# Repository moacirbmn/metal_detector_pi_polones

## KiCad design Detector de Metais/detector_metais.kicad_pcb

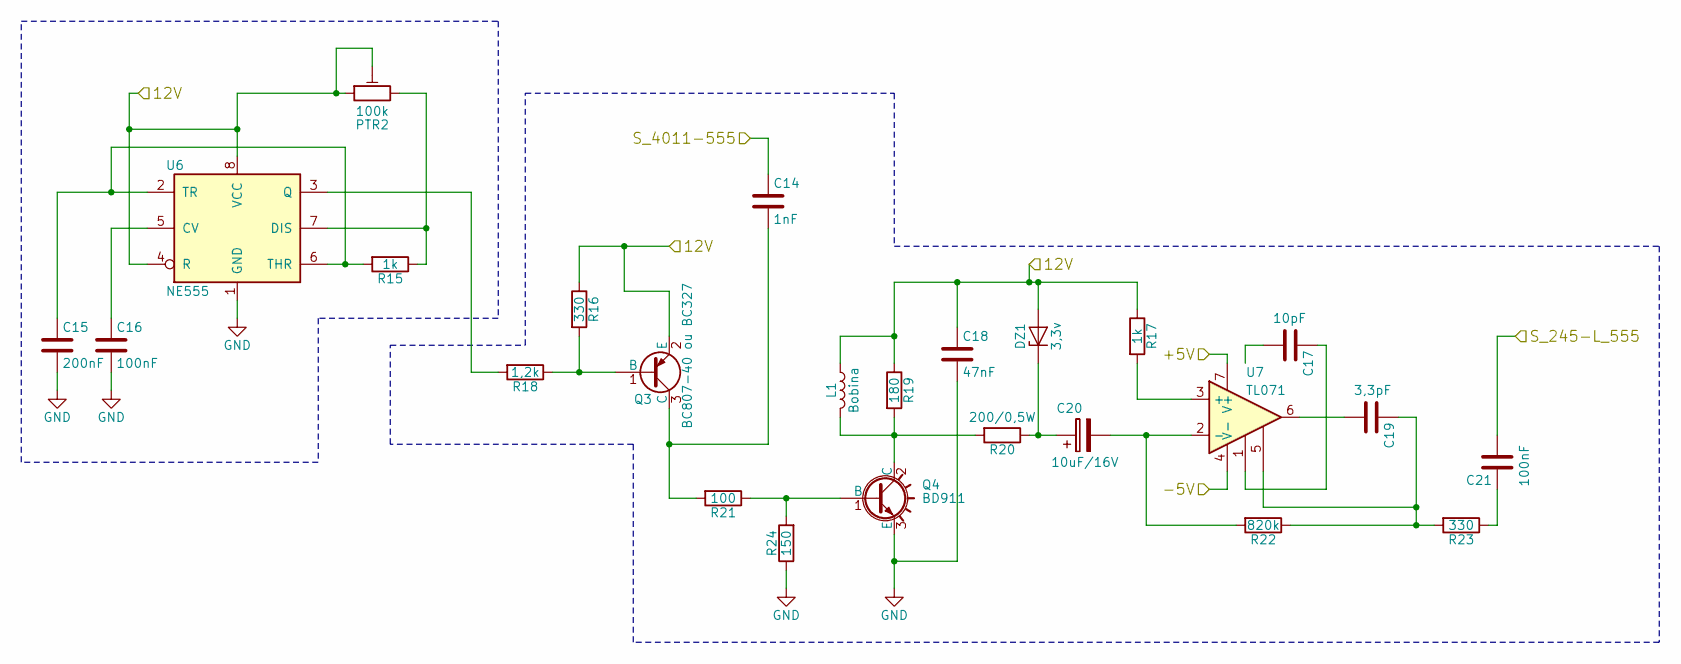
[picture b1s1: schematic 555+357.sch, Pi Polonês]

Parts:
C14: 1nF; C_Disc_D9.0mm_W5.0mm_P5.00mm
C15: 200nF; C_Disc_D6.0mm_W2.5mm_P5.00mm
C16, C21: 100nF; C_Disc_D4.3mm_W1.9mm_P5.00mm
C17: 10pF; C_Disc_D6.0mm_W2.5mm_P5.00mm
C18: 47nF; C_Disc_D6.0mm_W2.5mm_P5.00mm
C19: 3,3pF; C_Disc_D6.0mm_W2.5mm_P5.00mm
C20: 10uF/16V; C_Disc_D6.0mm_W2.5mm_P5.00mm
DZ1: 3,3v; D_A-405_P2.54mm_Vertical_AnodeUp
L1: Bobina; BarrelJack_Horizontal
PTR2: 100k; Potentiometer_ACP_CA9-H3,8_Horizontal
Q3: BC807-40 ou BC327; TO-92L
Q4: BD911; TO-220-3_Vertical
R15, R17: 1k; R_0805_2012Metric_Pad1.15x1.40mm_HandSolder
R16, R23: 330; R_0805_2012Metric_Pad1.15x1.40mm_HandSolder
R18: 1,2k; R_Axial_DIN0204_L3.6mm_D1.6mm_P1.90mm_Vertical
R19: 180; R_0805_2012Metric_Pad1.15x1.40mm_HandSolder
R20: 200/0,5W; R_Axial_DIN0207_L6.3mm_D2.5mm_P5.08mm_Vertical
R21: 100; R_0805_2012Metric_Pad1.15x1.40mm_HandSolder
R22: 820k; R_0805_2012Metric_Pad1.15x1.40mm_HandSolder
R24: 150; R_Axial_DIN0204_L3.6mm_D1.6mm_P1.90mm_Vertical
U6: NE555; HTSOP-8-1EP_3.9x4.9mm_P1.27mm_EP2.4x3.2mm
U7: TL071; DIP-8_W7.62mm_LongPads

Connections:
/555+357/12V: C18.1, DZ1.2 (A), L1.1, PTR2.1, PTR2.2, Q3.2 (E), R16.1, R17.1, R19.1, U6.4 (R), U6.8 (VCC); also elsewhere on the board
/555+357/+5V: U7.7 (V+); also elsewhere on the board
/555+357/-5V: U7.4 (V-); also elsewhere on the board
/555+357/S_245-L_555: C21.2; also elsewhere on the board
/4011/S_4011-555: C14.1; also elsewhere on the board
GND: C15.2, C16.2, C18.2, Q4.3 (E), R24.1, U6.1 (GND); also elsewhere on the board
unnamed: C14.2, Q3.3 (C), R21.2
unnamed: C15.1, R15.2, U6.2 (TR), U6.6 (THR)
unnamed: C16.1, U6.5 (CV)
unnamed: C17.1, U7.1
unnamed: C17.2, U7.8 (NC)
unnamed: C19.1, R22.1, R23.2, U7.5
unnamed: C19.2, U7.6
unnamed: C20.1, DZ1.1 (K), R20.1
unnamed: C20.2, R22.2, U7.2 (-)
unnamed: C21.1, R23.1
unnamed: L1.2, Q4.2 (C), R19.2, R20.2
unnamed: PTR2.3, R15.1, U6.7 (DIS)
unnamed: Q3.1 (B), R16.2, R18.1
unnamed: Q4.1 (B), R21.1, R24.2
unnamed: R17.2, U7.3 (+)
unnamed: R18.2, U6.3 (Q)

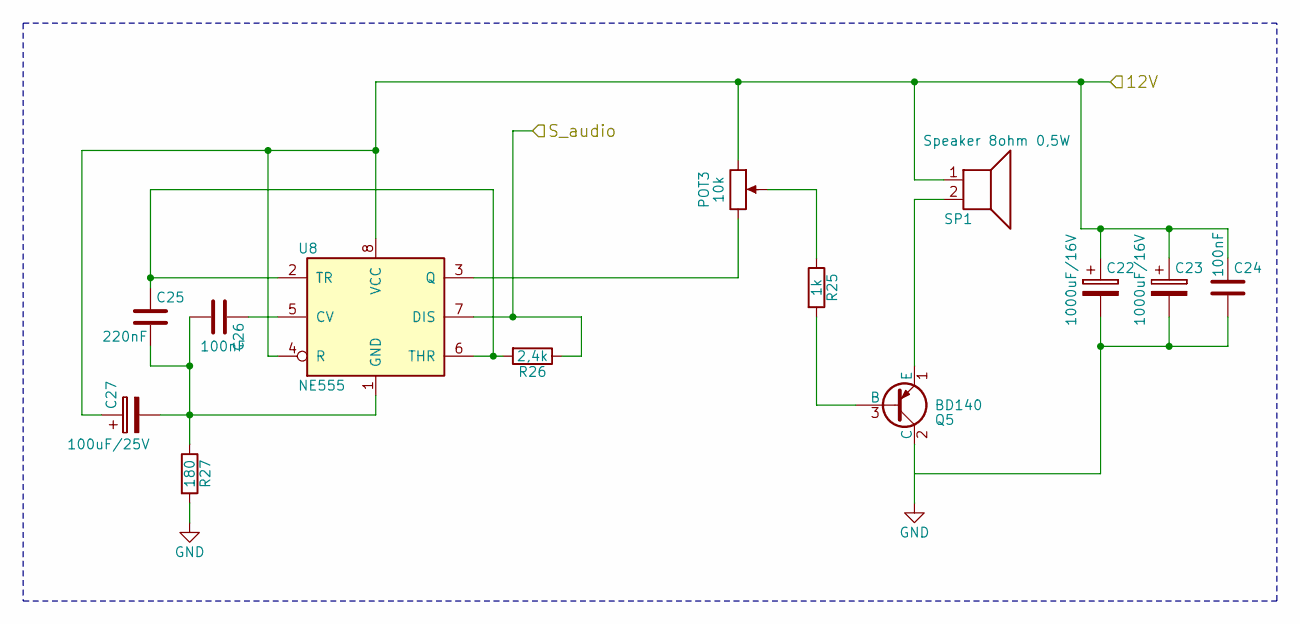
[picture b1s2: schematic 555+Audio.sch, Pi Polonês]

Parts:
C22, C23: 1000uF/16V; CP_Axial_L10.0mm_D6.0mm_P15.00mm_Horizontal
C24, C26: 100nF; C_Disc_D4.3mm_W1.9mm_P5.00mm
C25: 220nF; C_Disc_D6.0mm_W4.4mm_P5.00mm
C27: 100uF/25V; CP_Radial_D6.3mm_P2.50mm
POT3: 10k; Potentiometer_Vishay_148-149_Single_Horizontal
Q5: BD140; TO-126-3_Vertical
R25: 1k; R_0805_2012Metric_Pad1.15x1.40mm_HandSolder
R26: 2,4k; R_Axial_DIN0204_L3.6mm_D1.6mm_P1.90mm_Vertical
R27: 180; R_0805_2012Metric_Pad1.15x1.40mm_HandSolder
SP1: Speaker 8ohm 0,5W; PinHeader_1x02_P1.27mm_Horizontal
U8: NE555; HTSOP-8-1EP_3.9x4.9mm_P1.27mm_EP2.4x3.2mm

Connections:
/555+357/12V: C22.1, C23.1, C24.1, C27.1, POT3.1, SP1.1, U8.4 (R), U8.8 (VCC); also elsewhere on the board
/555+Audio/S_audio: R26.1, U8.7 (DIS); also elsewhere on the board
GND: Q5.2 (C), R27.2; also elsewhere on the board
unnamed: C22.2, C23.2, C24.2
unnamed: C25.1, R26.2, U8.2 (TR), U8.6 (THR)
unnamed: C25.2, C26.2, C27.2, R27.1, U8.1 (GND)
unnamed: C26.1, U8.5 (CV)
unnamed: POT3.2, R25.1
unnamed: POT3.3, U8.3 (Q)
unnamed: Q5.1 (E), SP1.2
unnamed: Q5.3 (B), R25.2

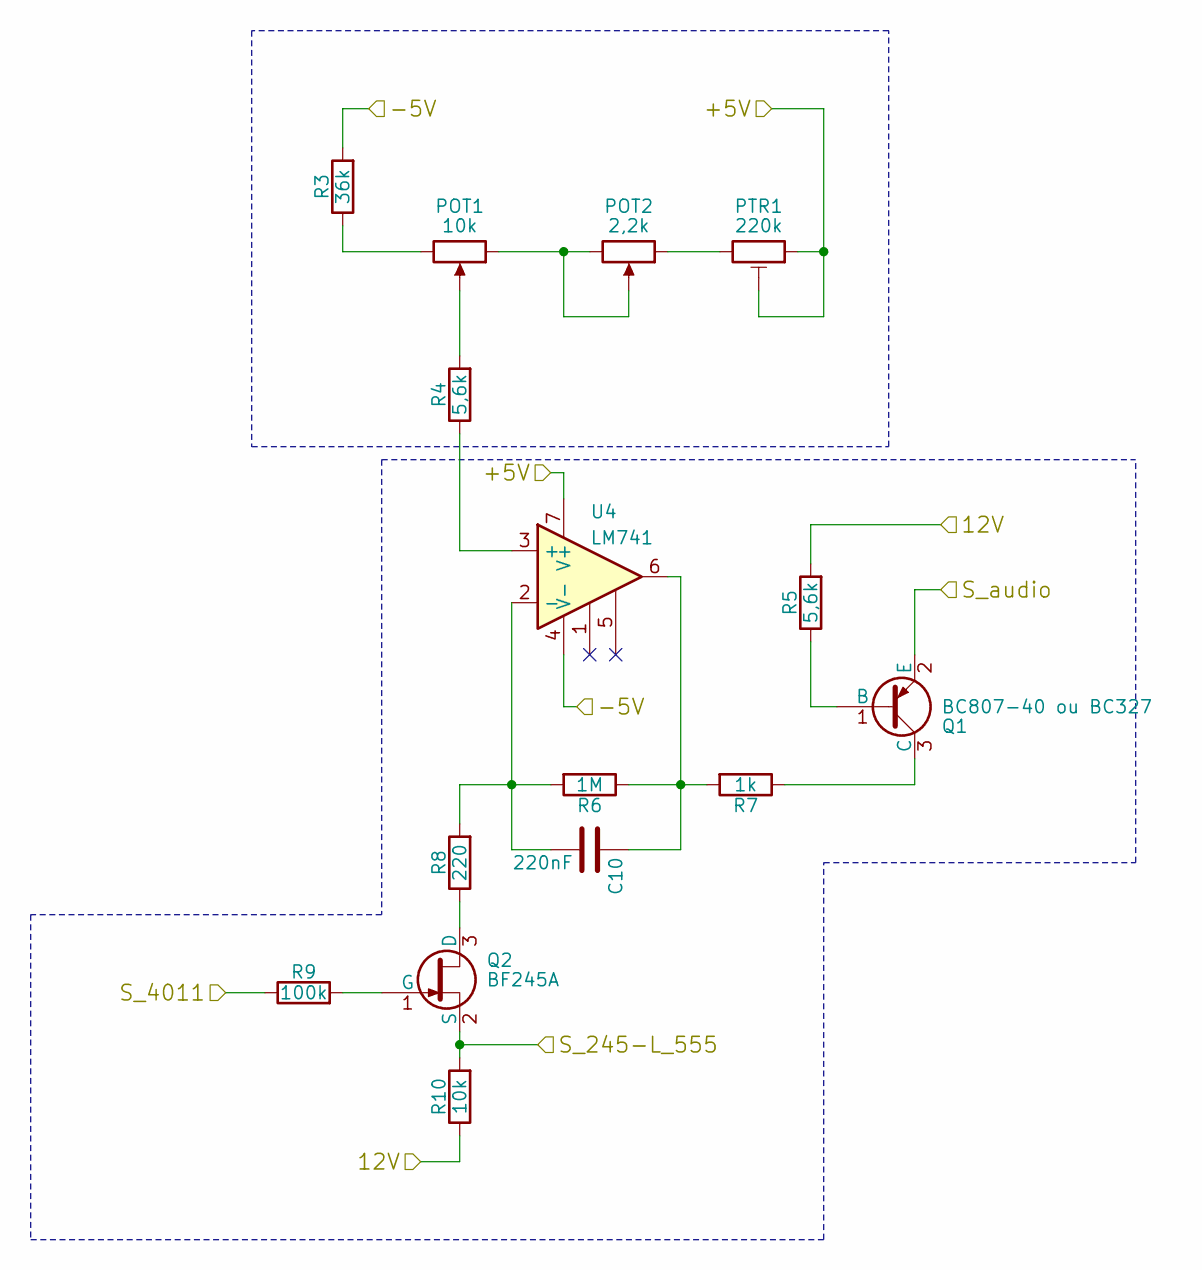
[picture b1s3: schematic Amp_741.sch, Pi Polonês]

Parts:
C10: 220nF; C_Disc_D6.0mm_W4.4mm_P5.00mm
POT1: 10k; Potentiometer_Vishay_148-149_Single_Horizontal
POT2: 2,2k; Potentiometer_Vishay_148-149_Single_Horizontal
PTR1: 220k; Potentiometer_ACP_CA9-H3,8_Horizontal
Q1: BC807-40 ou BC327; TO-92
Q2: BF245A; TO-92
R3: 36k; R_Axial_DIN0204_L3.6mm_D1.6mm_P1.90mm_Vertical
R4, R5: 5,6k; R_0805_2012Metric_Pad1.15x1.40mm_HandSolder
R6: 1M; R_0805_2012Metric_Pad1.15x1.40mm_HandSolder
R7: 1k; R_0805_2012Metric_Pad1.15x1.40mm_HandSolder
R8: 220; R_0805_2012Metric_Pad1.15x1.40mm_HandSolder
R9: 100k; R_0805_2012Metric_Pad1.15x1.40mm_HandSolder
R10: 10k; R_0805_2012Metric_Pad1.15x1.40mm_HandSolder
U4: LM741; DIP-8_W7.62mm_LongPads

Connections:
/555+357/12V: R5.2, R10.1; also elsewhere on the board
/555+357/+5V: PTR1.1, PTR1.2, U4.7 (V+); also elsewhere on the board
/555+357/-5V: R3.2, U4.4 (V-); also elsewhere on the board
/555+357/S_245-L_555: Q2.2 (S), R10.2; also elsewhere on the board
/555+Audio/S_audio: Q1.2 (E); also elsewhere on the board
/4011/S_4011: R9.1; also elsewhere on the board
unnamed: C10.1, R6.1, R7.2, U4.6
unnamed: C10.2, R6.2, R8.2, U4.2 (-)
unnamed: POT1.1, POT2.2, POT2.3
unnamed: POT1.2, R4.2
unnamed: POT1.3, R3.1
unnamed: POT2.1, PTR1.3
unnamed: Q1.1 (B), R5.1
unnamed: Q1.3 (C), R7.1
unnamed: Q2.1 (G), R9.2
unnamed: Q2.3 (D), R8.1
unnamed: R4.1, U4.3 (+)

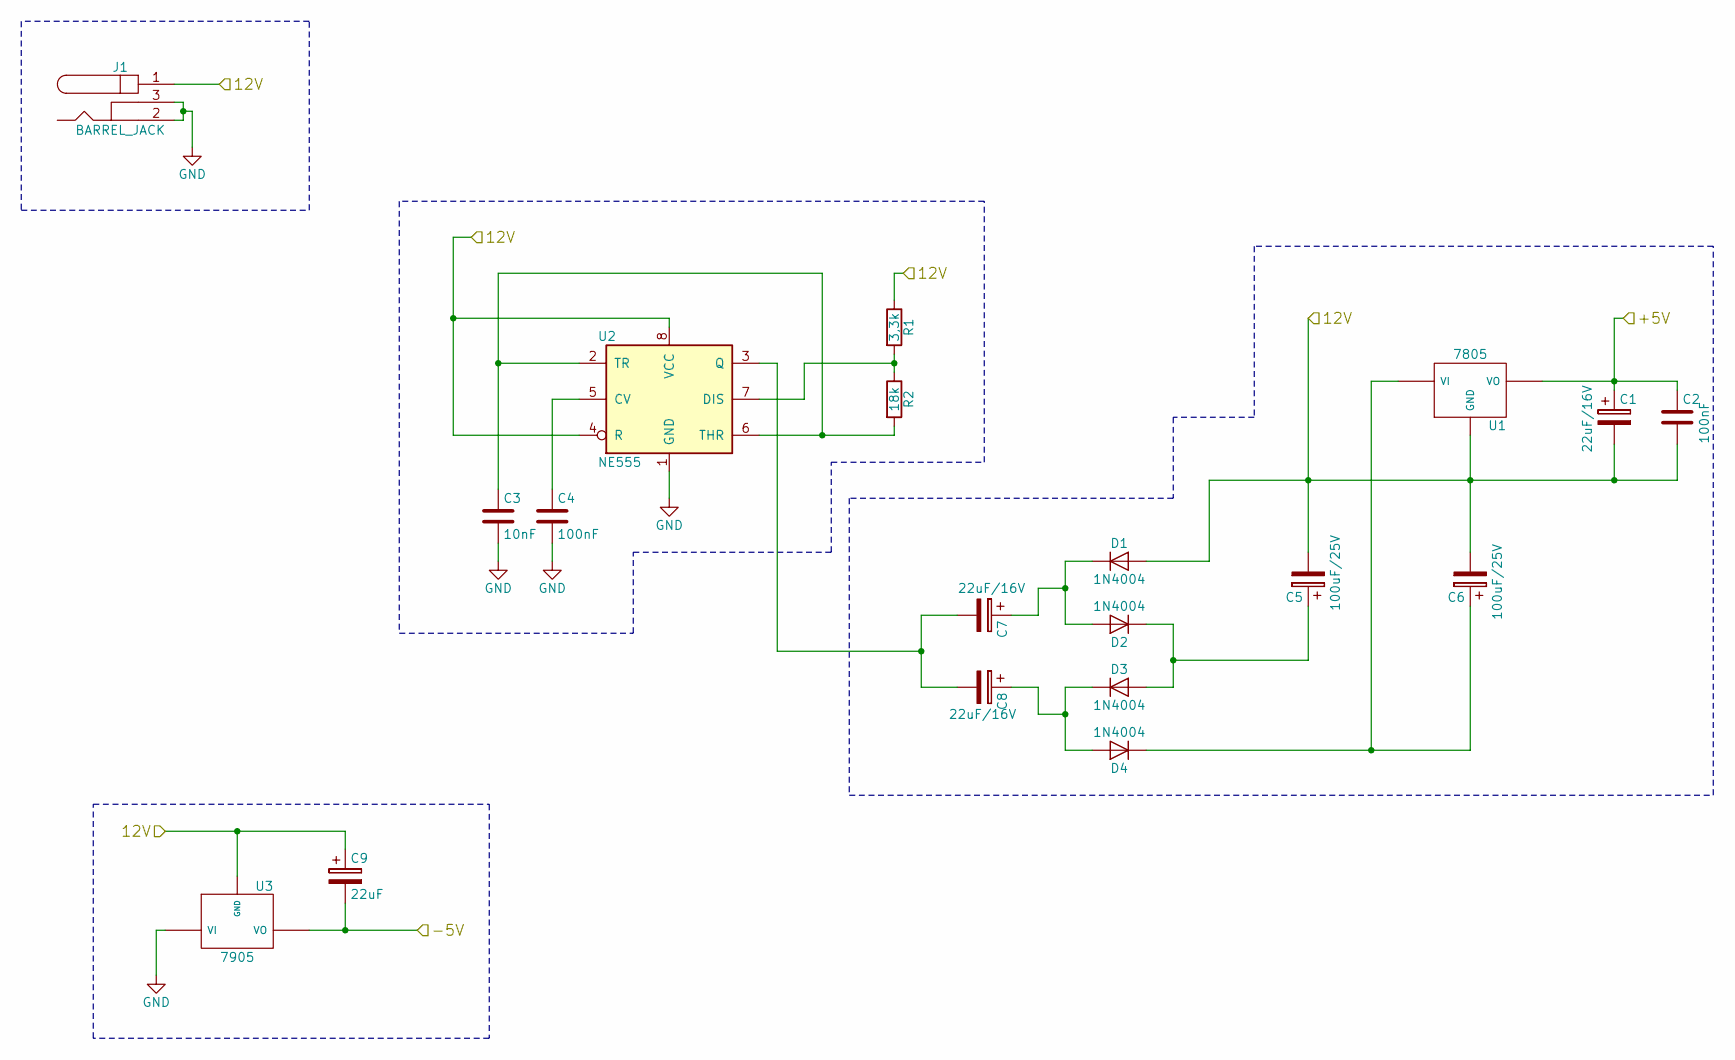
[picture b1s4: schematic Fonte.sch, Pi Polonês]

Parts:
C1, C7, C8: 22uF/16V; CP_Radial_D5.0mm_P2.50mm
C2, C4: 100nF; C_Disc_D4.3mm_W1.9mm_P5.00mm
C3: 10nF; C_Disc_D4.3mm_W1.9mm_P5.00mm
C5, C6: 100uF/25V; CP_Radial_D6.3mm_P2.50mm
C9: 22uF; C_Disc_D6.0mm_W2.5mm_P5.00mm
D1, D2, D3, D4: 1N4004; D_DO-41_SOD81_P2.54mm_Vertical_AnodeUp
J1: BARREL_JACK; BarrelJack_Horizontal
R1: 3,3k; R_0805_2012Metric_Pad1.15x1.40mm_HandSolder
R2: 18k; R_0805_2012Metric_Pad1.15x1.40mm_HandSolder
U1: 7805; TO-220-3_Vertical
U2: NE555; SOIC-8_3.9x4.9mm_P1.27mm
U3: 7905; TO-220-3_Vertical

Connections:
/555+357/12V: C1.2, C2.2, C5.2, C6.2, C9.1, D1.2 (A), J1.1, R1.1, U1.2 (GND), U2.4 (R), U2.8 (VCC), U3.2 (GND); also elsewhere on the board
/555+357/+5V: C1.1, C2.1, U1.3 (VO); also elsewhere on the board
/555+357/-5V: C9.2, U3.3 (VO); also elsewhere on the board
GND: C3.2, C4.2, J1.2, J1.3, U2.1 (GND), U3.1 (VI); also elsewhere on the board
unnamed: C3.1, R2.2, U2.2 (TR), U2.6 (THR)
unnamed: C4.1, U2.5 (CV)
unnamed: C5.1, D2.1 (K), D3.2 (A)
unnamed: C6.1, D4.1 (K), U1.1 (VI)
unnamed: C7.1, D1.1 (K), D2.2 (A)
unnamed: C7.2, C8.2, U2.3 (Q)
unnamed: C8.1, D3.1 (K), D4.2 (A)
unnamed: R1.2, R2.1, U2.7 (DIS)

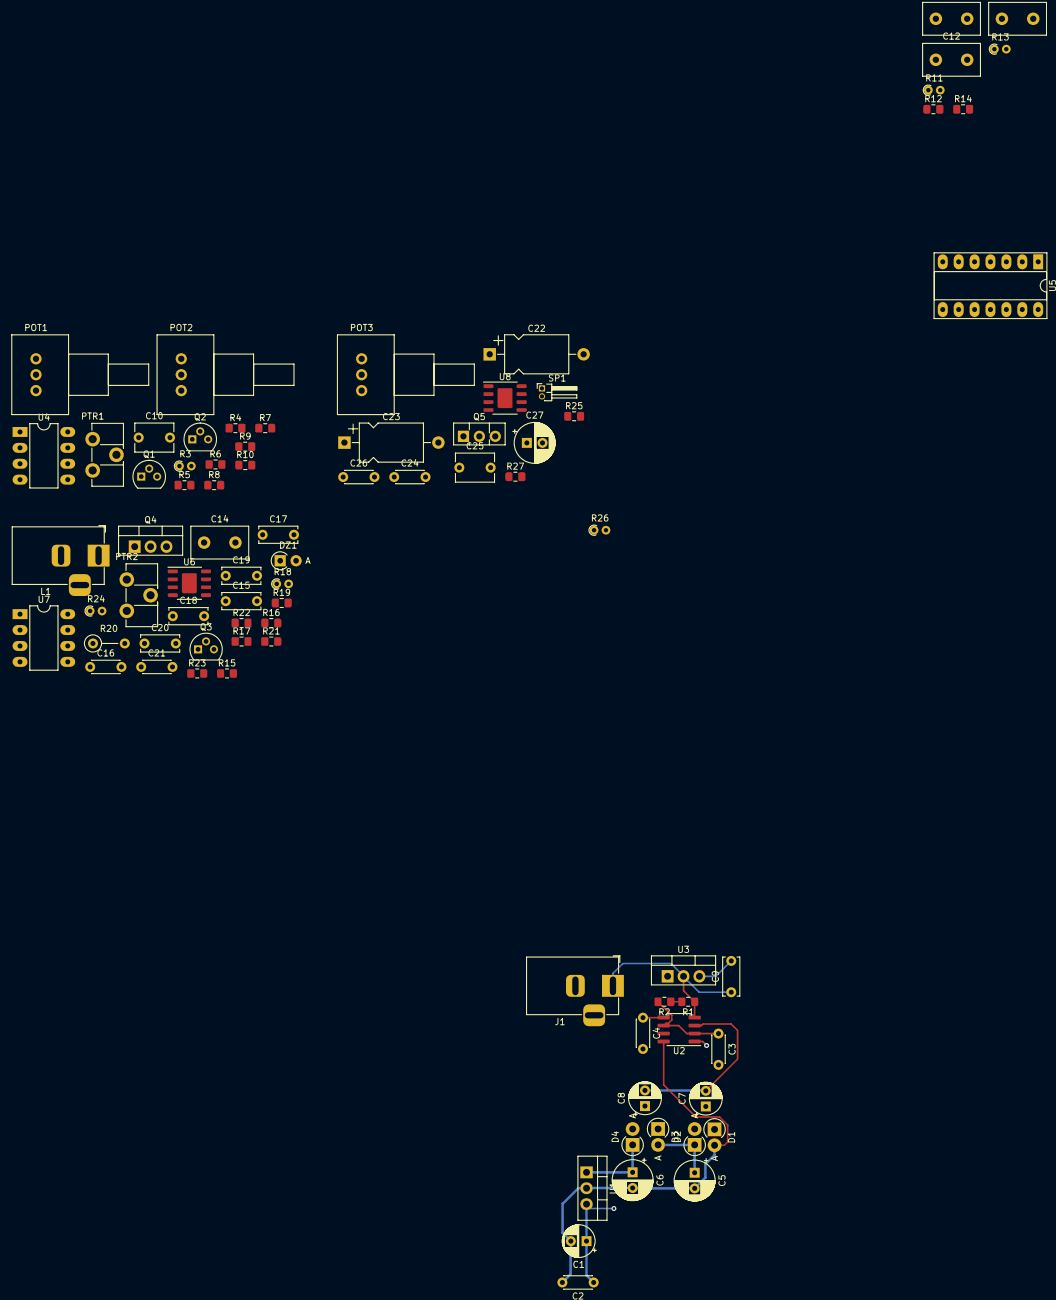
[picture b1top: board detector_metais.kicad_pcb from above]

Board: 2 copper layers, 80 parts (0 on the bottom side), 57 nets.

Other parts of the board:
C11, C12, C13: 1nF; C_Disc_D9.0mm_W5.0mm_P5.00mm
R11, R13: 33k; R_Axial_DIN0204_L3.6mm_D1.6mm_P1.90mm_Vertical
R12, R14: 47k; R_0805_2012Metric_Pad1.15x1.40mm_HandSolder
U5: 4011; DIP-14_W7.62mm_Socket_LongPads

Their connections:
/4011/S_4011: C13.2, U5.10; also elsewhere on the board
/4011/S_4011-555: R11.1, U5.1, U5.2; also elsewhere on the board
GND: R13.2, R14.2; also elsewhere on the board
unnamed: C11.1, R12.1, U5.8, U5.9
unnamed: C11.2, C12.2, U5.3
unnamed: C12.1, R13.1, U5.5, U5.6
unnamed: C13.1, R14.1, U5.12, U5.13
unnamed: R11.2, U5.4
unnamed: R12.2, U5.11

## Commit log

2017-10-12 esquematico e BOM html
2017-10-12 Esquematico em pdf
2019-10-30 atualizando lista de componentes
2019-11-11 Atualizando simbolos e criando footprint
2019-11-11 Desenhando fonte
